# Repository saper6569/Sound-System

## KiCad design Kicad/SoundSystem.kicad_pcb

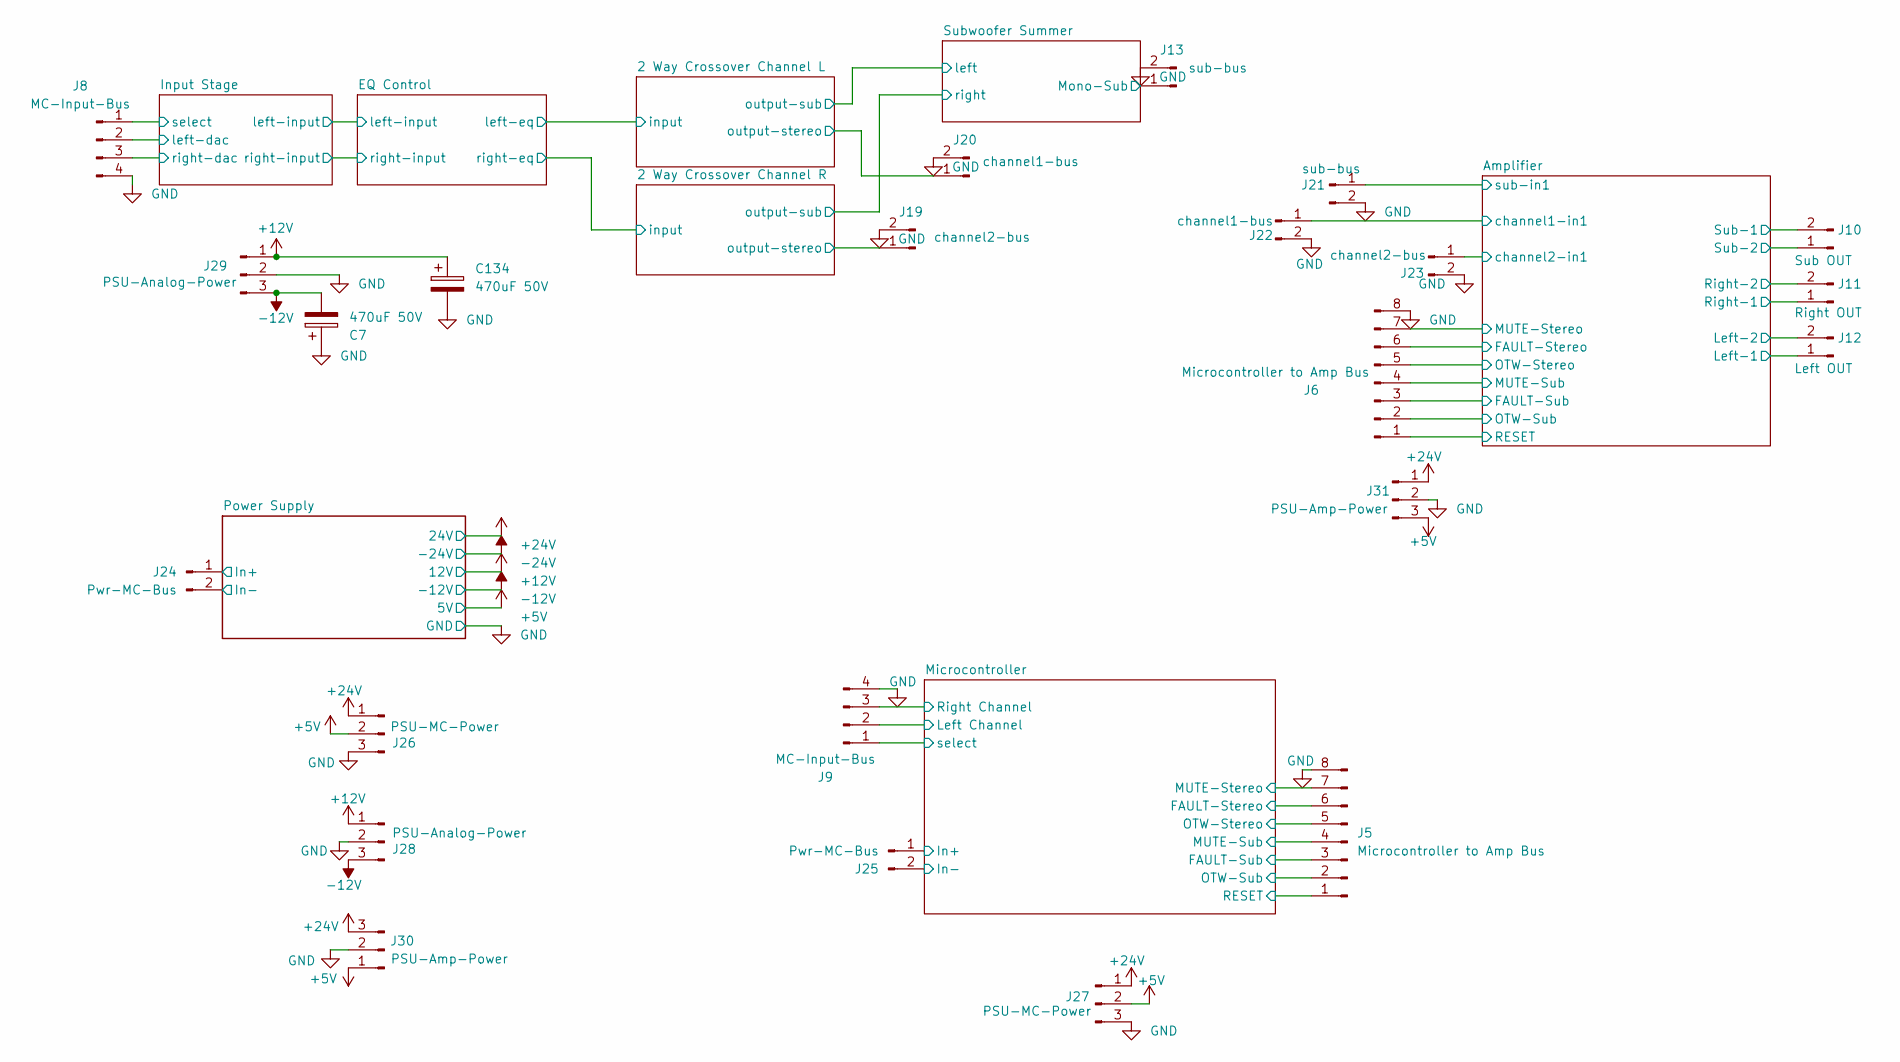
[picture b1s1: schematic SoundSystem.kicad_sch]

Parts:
C7, C134: 470uF 50V; CP_Radial_D12.5mm_P5.00mm; MPN NXH 50V470 12.5*20; LCSC C165672
J5, J6: Microcontroller to Amp Bus; PinHeader_1x08_P2.54mm_Vertical; MPN PZ254V-11-08P; LCSC C492407
J8, J9: MC-Input-Bus; PinHeader_1x04_P2.54mm_Vertical; MPN PZ254V-11-04P; LCSC C492403
J10: Sub OUT; TerminalBlock_Phoenix_MKDS-1,5-2-5.08_1x02_P5.08mm_Horizont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; MPN KF128-5.08-2P-AA; LCSC C474952
J11: Right OUT; TerminalBlock_Phoenix_MKDS-1,5-2-5.08_1x02_P5.08mm_Horizont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; MPN KF128-5.08-2P-AA; LCSC C474952
J12: Left OUT; TerminalBlock_Phoenix_MKDS-1,5-2-5.08_1x02_P5.08mm_Horizont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; MPN KF128-5.08-2P-AA; LCSC C474952
J13, J21: sub-bus; PinHeader_1x02_P2.54mm_Vertical; MPN PZ254V-11-02P; LCSC C492401
J19, J23: channel2-bus; PinHeader_1x02_P2.54mm_Vertical; MPN PZ254V-11-02P; LCSC C492401
J20, J22: channel1-bus; PinHeader_1x02_P2.54mm_Vertical; MPN PZ254V-11-02P; LCSC C492401
J24, J25: Pwr-MC-Bus; PinHeader_1x02_P2.54mm_Vertical; MPN PZ254V-11-02P; LCSC C492401
J26, J27: PSU-MC-Power; PinHeader_1x03_P2.54mm_Vertical; MPN PZ254V-11-03P; LCSC C2937625
J28, J29: PSU-Analog-Power; PinHeader_1x03_P2.54mm_Vertical; MPN PZ254V-11-03P; LCSC C2937625
J30, J31: PSU-Amp-Power; TerminalBlock_Phoenix_MKDS-1,5-3-5.08_1x03_P5.08mm_Horizont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; MPN KF128-5.08-3P-AA; LCSC C474953

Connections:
+12V: C134.1, J28.1, J29.1; also elsewhere on the board
-12V: C7.2, J28.3, J29.3; also elsewhere on the board
/2 Way Crossover Channel L/output-stereo: J20.1; also elsewhere on the board
/2 Way Crossover Channel R/output-stereo: J19.1; also elsewhere on the board
/Amplifier/FAULT-Stereo: J6.6; also elsewhere on the board
/Amplifier/FAULT-Sub: J6.3; also elsewhere on the board
/Amplifier/Left-1: J12.1; also elsewhere on the board
/Amplifier/Left-2: J12.2; also elsewhere on the board
/Amplifier/MUTE-Stereo: J6.7; also elsewhere on the board
/Amplifier/MUTE-Sub: J6.4; also elsewhere on the board
/Amplifier/OTW-Stereo: J6.5; also elsewhere on the board
/Amplifier/OTW-Sub: J6.2; also elsewhere on the board
/Amplifier/Right-1: J11.1; also elsewhere on the board
/Amplifier/Right-2: J11.2; also elsewhere on the board
/Amplifier/Sub-1: J10.2; also elsewhere on the board
/Amplifier/Sub-2: J10.1; also elsewhere on the board
/Amplifier/channel1-in1: J22.1; also elsewhere on the board
/Amplifier/channel2-in1: J23.1; also elsewhere on the board
/Amplifier/sub-in1: J21.1; also elsewhere on the board
/Input Stage/left-dac: J8.2; also elsewhere on the board
/Input Stage/right-dac: J8.3; also elsewhere on the board
/Input Stage/select: J8.1; also elsewhere on the board
/Microcontroller/FAULT-Stereo: J5.5; also elsewhere on the board
/Microcontroller/FAULT-Sub: J5.3; also elsewhere on the board
/Microcontroller/In+: J25.1; also elsewhere on the board
/Microcontroller/In-: J25.2; also elsewhere on the board
/Microcontroller/Left Channel: J9.2; also elsewhere on the board
/Microcontroller/MUTE-Stereo: J5.7; also elsewhere on the board
/Microcontroller/MUTE-Sub: J5.4; also elsewhere on the board
/Microcontroller/OTW-Stereo: J5.6; also elsewhere on the board
/Microcontroller/OTW-Sub: J5.2; also elsewhere on the board
/Microcontroller/RESET: J5.1; also elsewhere on the board
/Microcontroller/Right Channel: J9.3; also elsewhere on the board
/Microcontroller/select: J9.1; also elsewhere on the board
/Power Supply/In+: J24.1; also elsewhere on the board
/Subwoofer Summer/Mono-Sub: J13.1; also elsewhere on the board
GND: C7.1, C134.2, J5.8, J6.8, J8.4, J9.4, J13.2, J19.2, J20.2, J21.2, J22.2, J23.2, J26.3, J27.3, J28.2, J29.2, J30.2, J31.2; also elsewhere on the board
RESET: J6.1; also elsewhere on the board

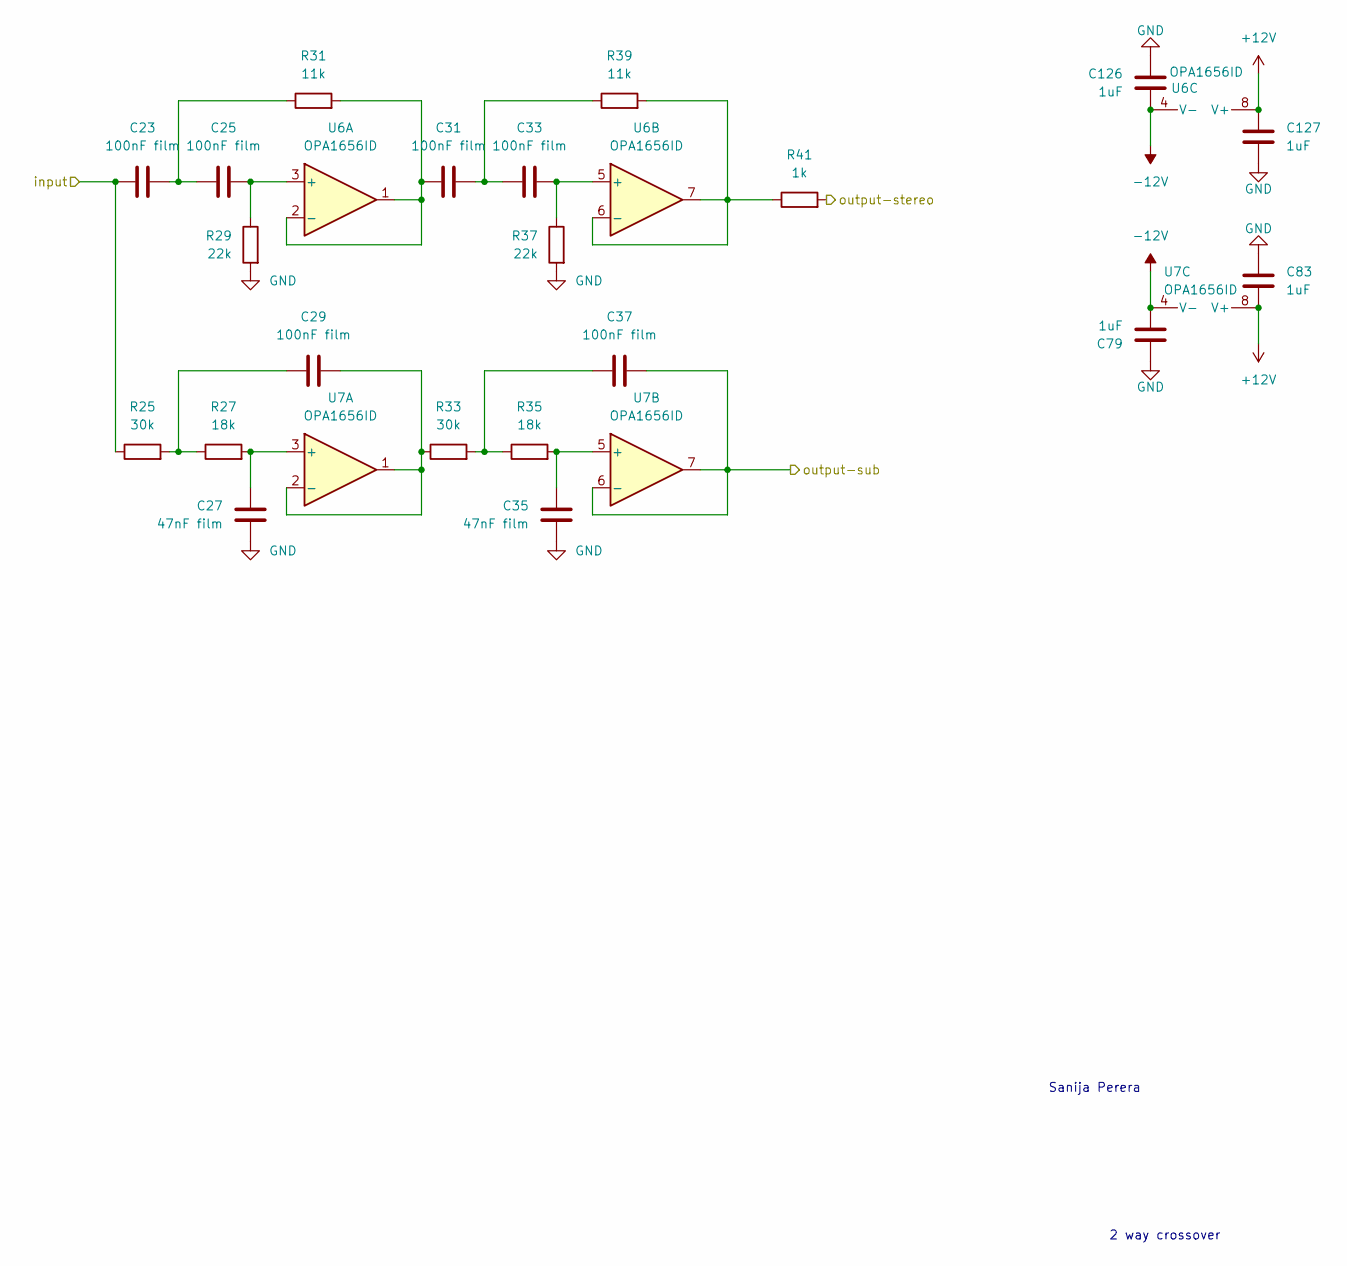
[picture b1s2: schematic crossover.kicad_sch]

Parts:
C23, C25, C29, C31, C33, C37: 100nF film; C_Rect_L7.2mm_W3.5mm_P5.00mm_FKS2_FKP2_MKS2_MKP2; MPN MKS2D031001A00JSSD; LCSC C415551
C27, C35: 47nF film; C_Rect_L7.2mm_W4.5mm_P5.00mm_FKS2_FKP2_MKS2_MKP2; MPN C242A473J20A201; LCSC C328859
C79, C83, C126, C127: 1uF; C_0805_2012Metric_Pad1.18x1.45mm_HandSolder; MPN CC0805KKX7R9BB105; LCSC C91185
R25, R33: 30k; R_0805_2012Metric_Pad1.20x1.40mm_HandSolder; MPN 0805W8F3002T5E; LCSC C17621
R27, R35: 18k; R_0805_2012Metric_Pad1.20x1.40mm_HandSolder; MPN 0805W8F1802T5E; LCSC C17506
R29, R37: 22k; R_0805_2012Metric_Pad1.20x1.40mm_HandSolder; MPN 0805W8F2202T5E; LCSC C17560
R31, R39: 11k; R_0805_2012Metric_Pad1.20x1.40mm_HandSolder; MPN 0805W8F1102T5E; LCSC C17429
R41: 1k; R_0805_2012Metric_Pad1.20x1.40mm_HandSolder; MPN 0805W8F1001T5E; LCSC C17513
U6, U7: OPA1656ID; SOIC-8_3.9x4.9mm_P1.27mm; MPN OPA1656IDR; LCSC C1849431

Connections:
+12V: C83.2, C127.2, U6.8 (V+), U7.8 (V+); also elsewhere on the board
-12V: C79.1, C126.1, U6.4 (V-), U7.4 (V-); also elsewhere on the board
/2 Way Crossover Channel L/input: C23.1, R25.1; also elsewhere on the board
/2 Way Crossover Channel L/output-stereo: R41.2; also elsewhere on the board
/2 Way Crossover Channel L/output-sub: C37.2, U7.6 (-), U7.7; also elsewhere on the board
GND: C27.1, C35.1, C79.2, C83.1, C126.2, C127.1, R29.2, R37.2; also elsewhere on the board
unnamed: C23.2, C25.1, R31.1
unnamed: C29.1, R25.2, R27.1
unnamed: C31.2, C33.1, R39.1
unnamed: C37.1, R33.2, R35.1
unnamed: C25.2, R29.1, U6.3 (+)
unnamed: C31.1, R31.2, U6.1, U6.2 (-)
unnamed: C33.2, R37.1, U6.5 (+)
unnamed: R39.2, R41.1, U6.6 (-), U6.7
unnamed: C27.2, R27.2, U7.3 (+)
unnamed: C29.2, R33.1, U7.1, U7.2 (-)
unnamed: C35.2, R35.2, U7.5 (+)

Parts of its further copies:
C24, C26, C30, C32, C34, C38: 100nF film; C_Rect_L7.2mm_W3.5mm_P5.00mm_FKS2_FKP2_MKS2_MKP2; MPN MKS2D031001A00JSSD; LCSC C415551
C28, C36: 47nF film; C_Rect_L7.2mm_W4.5mm_P5.00mm_FKS2_FKP2_MKS2_MKP2; MPN C242A473J20A201; LCSC C328859
C84, C85, C128, C129: 1uF; C_0805_2012Metric_Pad1.18x1.45mm_HandSolder; MPN CC0805KKX7R9BB105; LCSC C91185
R26, R34: 30k; R_0805_2012Metric_Pad1.20x1.40mm_HandSolder; MPN 0805W8F3002T5E; LCSC C17621
R28, R36: 18k; R_0805_2012Metric_Pad1.20x1.40mm_HandSolder; MPN 0805W8F1802T5E; LCSC C17506
R30, R38: 22k; R_0805_2012Metric_Pad1.20x1.40mm_HandSolder; MPN 0805W8F2202T5E; LCSC C17560
R32, R40: 11k; R_0805_2012Metric_Pad1.20x1.40mm_HandSolder; MPN 0805W8F1102T5E; LCSC C17429
R42: 1k; R_0805_2012Metric_Pad1.20x1.40mm_HandSolder; MPN 0805W8F1001T5E; LCSC C17513
U8, U9: OPA1656ID; SOIC-8_3.9x4.9mm_P1.27mm; MPN OPA1656IDR; LCSC C1849431

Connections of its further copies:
+12V: C85.2, C129.2, U8.8 (V+), U9.8 (V+); also elsewhere on the board
-12V: C84.1, C128.1, U8.4 (V-), U9.4 (V-); also elsewhere on the board
/2 Way Crossover Channel R/input: C24.1, R26.1; also elsewhere on the board
/2 Way Crossover Channel R/output-stereo: R42.2; also elsewhere on the board
/2 Way Crossover Channel R/output-sub: C38.2, U9.6 (-), U9.7; also elsewhere on the board
GND: C28.1, C36.1, C84.2, C85.1, C128.2, C129.1, R30.2, R38.2; also elsewhere on the board
unnamed: C24.2, C26.1, R32.1
unnamed: C30.1, R26.2, R28.1
unnamed: C32.2, C34.1, R40.1
unnamed: C38.1, R34.2, R36.1
unnamed: C26.2, R30.1, U8.3 (+)
unnamed: C32.1, R32.2, U8.1, U8.2 (-)
unnamed: C34.2, R38.1, U8.5 (+)
unnamed: R40.2, R42.1, U8.6 (-), U8.7
unnamed: C28.2, R28.2, U9.3 (+)
unnamed: C30.2, R34.1, U9.1, U9.2 (-)
unnamed: C36.2, R36.2, U9.5 (+)

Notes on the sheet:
2 way crossover
Sanija Perera

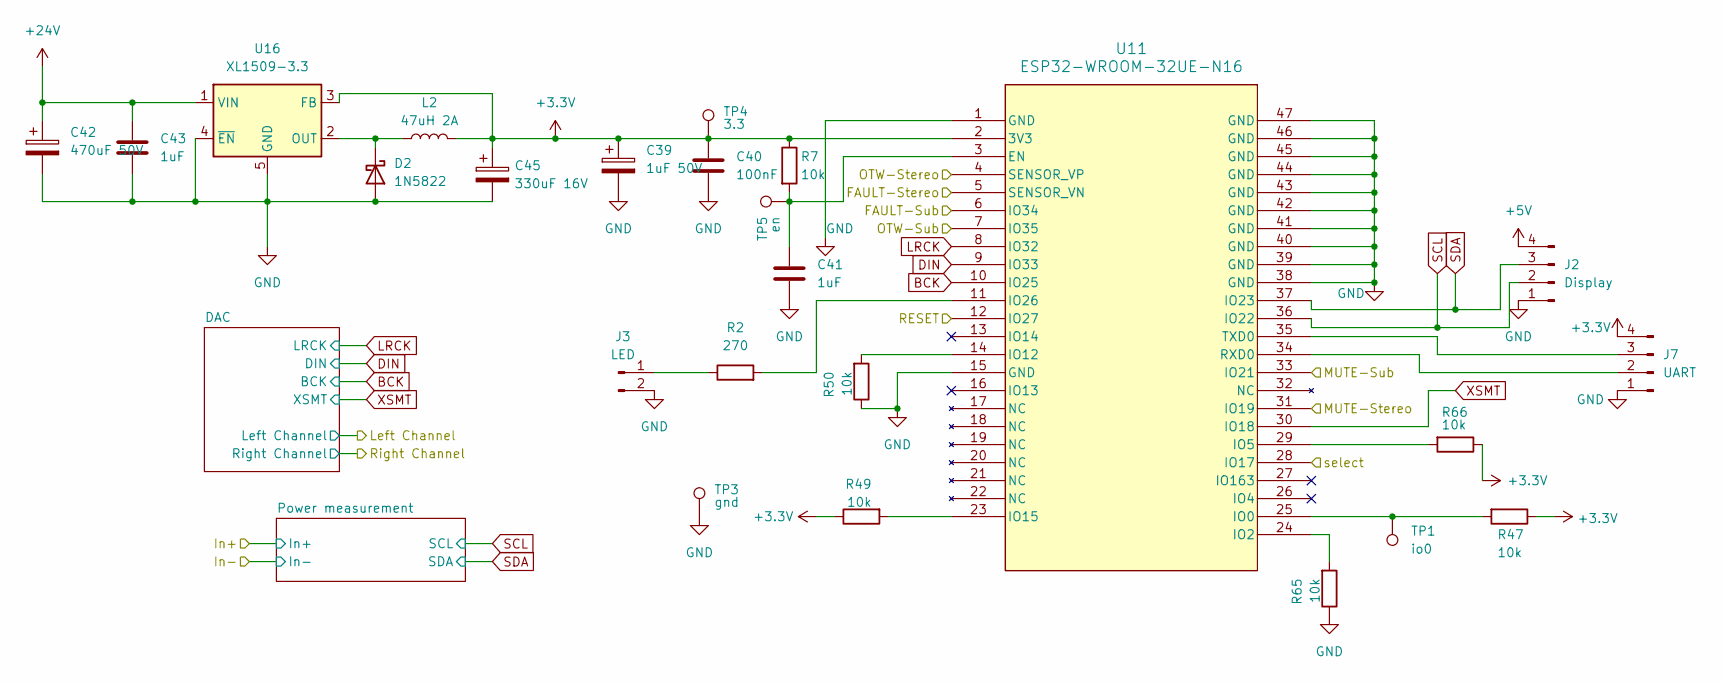
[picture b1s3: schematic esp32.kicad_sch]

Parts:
C39: 1uF 50V; CP_Elec_4x5.4; MPN MVK50V1M4*5 4.0TP; LCSC C346963
C40: 100nF; C_0805_2012Metric_Pad1.18x1.45mm_HandSolder; MPN CC0805KRX7R9BB104; LCSC C49678
C41: 1uF; C_0805_2012Metric_Pad1.18x1.45mm_HandSolder; MPN CC0805KKX7R9BB105; LCSC C91185
C42: 470uF 50V; CP_Radial_D12.5mm_P5.00mm; MPN NXH 50V470 12.5*20; LCSC C165672
C43: 1uF; C_1206_3216Metric_Pad1.33x1.80mm_HandSolder; MPN CC1206KKX7R9BB105; LCSC C107185
C45: 330uF 16V; CP_Elec_8x10; MPN MVK16V330M8*10 8.0TP; LCSC C2835680
D2: 1N5822; D_DO-27_P12.70mm_Horizontal; MPN 1N5822; LCSC C2476
J2: Display; PinHeader_1x04_P2.54mm_Vertical; MPN PZ254V-11-04P; LCSC C492403
J3: LED; PinHeader_1x02_P2.54mm_Vertical; MPN PZ254V-11-02P; LCSC C492401
J7: UART; PinHeader_1x04_P2.54mm_Vertical; MPN PZ254V-11-04P; LCSC C492403
L2: 47uH 2A; L_Bourns_SRR1260; MPN SRR1260-470M; LCSC C1329363
R2: 270; R_0805_2012Metric_Pad1.20x1.40mm_HandSolder; MPN 0805W8F2700T5E; LCSC C17590
R7, R47, R49, R50, R65, R66: 10k; R_0805_2012Metric_Pad1.20x1.40mm_HandSolder; MPN 0805W8F1002T5E; LCSC C17414
TP1: io0; TestPoint_Pad_1.0x1.0mm; MPN (PCB pad)
TP3: gnd; TestPoint_Pad_1.0x1.0mm; MPN (PCB pad)
TP4: 3.3; TestPoint_Pad_1.0x1.0mm; MPN (PCB pad)
TP5: en; TestPoint_Pad_1.0x1.0mm; MPN (PCB pad)
U11: ESP32-WROOM-32UE-N16; ESP32-32UE_EXP; MPN ESP32-WROOM-32UE-N16; LCSC C701346
U16: XL1509-3.3; SOIC-8_3.9x4.9mm_P1.27mm; MPN XL1509-3.3E1; LCSC C74193

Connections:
+3.3V: C39.1, C40.1, C45.1, J7.4, L2.2, R7.1, R47.1, R49.1, R66.1, TP4.1 (1_1), U11.2 (3V3), U16.3 (FB); also elsewhere on the board
/Microcontroller/FAULT-Stereo: U11.5 (SENSOR_VN); also elsewhere on the board
/Microcontroller/FAULT-Sub: U11.6 (IO34); also elsewhere on the board
/Microcontroller/MUTE-Stereo: U11.31 (IO19); also elsewhere on the board
/Microcontroller/MUTE-Sub: U11.33 (IO21); also elsewhere on the board
/Microcontroller/OTW-Stereo: U11.4 (SENSOR_VP); also elsewhere on the board
/Microcontroller/OTW-Sub: U11.7 (IO35); also elsewhere on the board
/Microcontroller/RESET: U11.12 (IO27); also elsewhere on the board
/Microcontroller/select: U11.28 (IO17); also elsewhere on the board
BCK: U11.10 (IO25); also elsewhere on the board
DIN: U11.9 (IO33); also elsewhere on the board
GND: C39.2, C40.2, C41.2, C42.2, C43.2, C45.2, D2.2 (A), J2.1, J3.2, J7.1, R50.1, R65.1, TP3.1 (1_1), U11.1 (GND), U11.15 (GND), U11.38 (GND), U11.39 (GND), U11.40 (GND), U11.41 (GND), U11.42 (GND), U11.43 (GND), U11.44 (GND), U11.45 (GND), U11.46 (GND), U11.47 (GND), U16.4 (~EN), U16.5 (GND), U16.6 (GND), U16.7 (GND), U16.8 (GND); also elsewhere on the board
LRCK: U11.8 (IO32); also elsewhere on the board
unnamed: D2.1 (K), L2.1, U16.2 (OUT)
unnamed: J3.1, R2.1
unnamed: J7.2, U11.34 (RXD0)
unnamed: J7.3, U11.35 (TXD0)
unnamed: C41.1, R7.2, TP5.1 (1_1), U11.3 (EN)
unnamed: R47.2, TP1.1 (1_1), U11.25 (IO0)
unnamed: R65.2, U11.24 (IO2)
unnamed: R66.2, U11.29 (IO5)
unnamed: R50.2, U11.14 (IO12)
unnamed: R49.2, U11.23 (IO15)
unnamed: R2.2, U11.11 (IO26)
SCL: J2.2, U11.36 (IO22); also elsewhere on the board
SDA: J2.3, U11.37 (IO23); also elsewhere on the board
XSMT: U11.30 (IO18); also elsewhere on the board

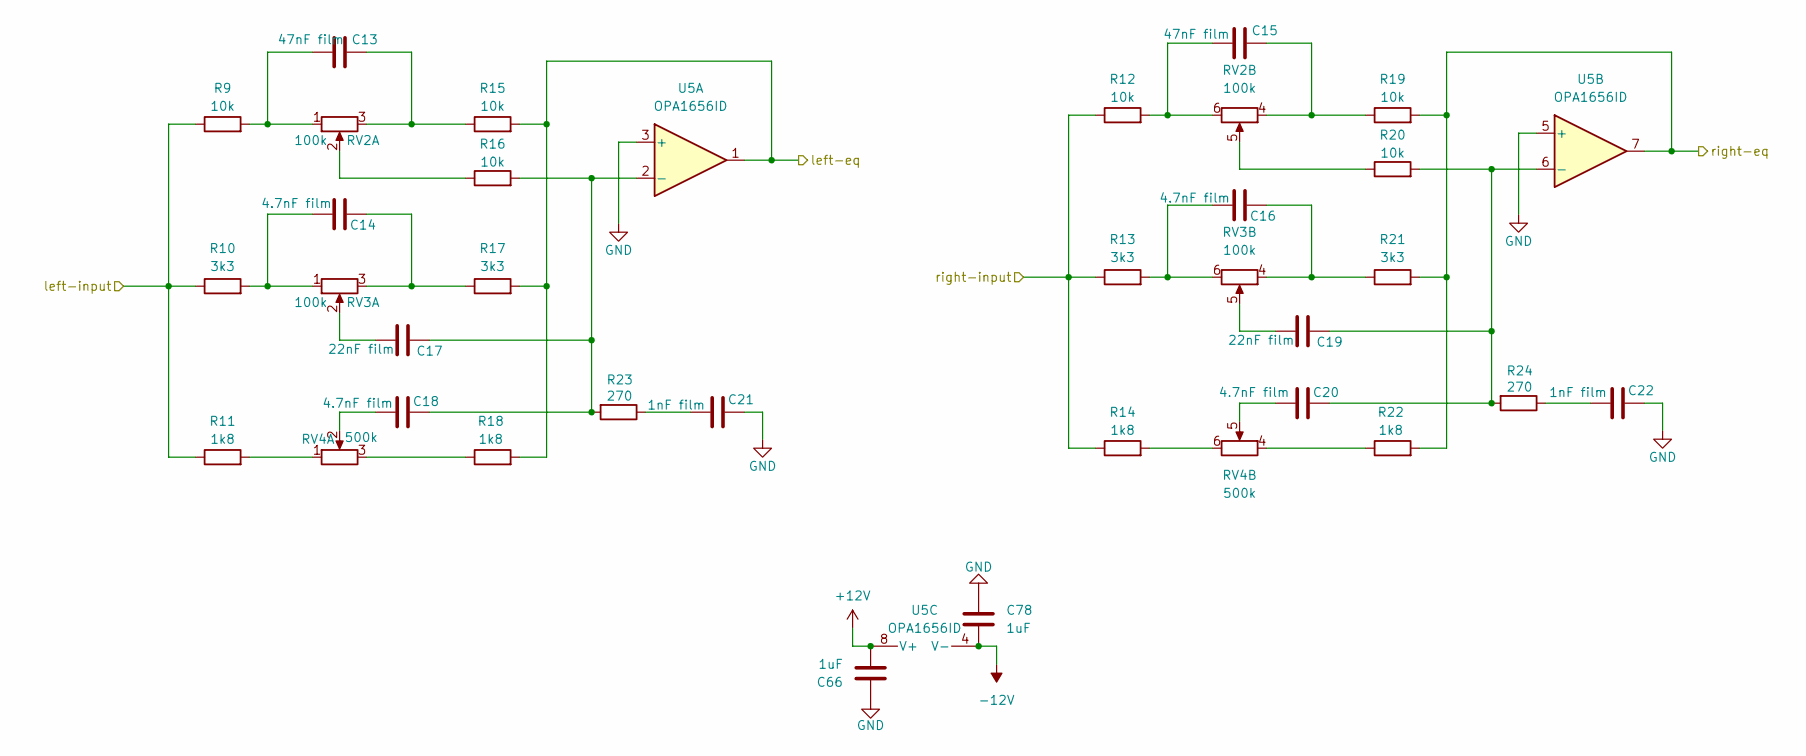
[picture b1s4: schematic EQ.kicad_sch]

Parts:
C13, C15: 47nF film; C_Rect_L7.2mm_W4.5mm_P5.00mm_FKS2_FKP2_MKS2_MKP2; MPN C242A473J20A201; LCSC C328859
C14, C16, C18, C20: 4.7nF film; C_Rect_L7.2mm_W3.5mm_P5.00mm_FKS2_FKP2_MKS2_MKP2; MPN C242A472J20A201; LCSC C401257
C17, C19: 22nF film; C_Rect_L7.2mm_W3.5mm_P5.00mm_FKS2_FKP2_MKS2_MKP2; MPN C242A223J20A201; LCSC C328834
C21, C22: 1nF film; C_Rect_L7.2mm_W3.5mm_P5.00mm_FKS2_FKP2_MKS2_MKP2; MPN C242A102J20C000; LCSC C280714
C66, C78: 1uF; C_0805_2012Metric_Pad1.18x1.45mm_HandSolder; MPN CC0805KKX7R9BB105; LCSC C91185
R9, R12, R15, R16, R19, R20: 10k; R_0805_2012Metric_Pad1.20x1.40mm_HandSolder; MPN 0805W8F1002T5E; LCSC C17414
R10, R13, R17, R21: 3k3; R_0805_2012Metric_Pad1.20x1.40mm_HandSolder; MPN 0805W8F3301T5E; LCSC C26010
R11, R14, R18, R22: 1k8; R_1206_3216Metric_Pad1.30x1.75mm_HandSolder; MPN 1206W4F1801T5E; LCSC C22108
R23, R24: 270; R_0805_2012Metric_Pad1.20x1.40mm_HandSolder; MPN 0805W8F2700T5E; LCSC C17590
RV2, RV3: 100k; 10k pot; MPN 16mm dual-gang pot (A10K / B100K / B100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
RV4: 500k; 10k pot; MPN 16mm dual-gang pot (A10K / B100K / B100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
U5: OPA1656ID; SOIC-8_3.9x4.9mm_P1.27mm; MPN OPA1656IDR; LCSC C1849431

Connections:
+12V: C66.1, U5.8 (V+); also elsewhere on the board
-12V: C78.2, U5.4 (V-); also elsewhere on the board
/2 Way Crossover Channel L/input: R15.2, R17.2, R18.2, U5.1; also elsewhere on the board
/2 Way Crossover Channel R/input: R19.2, R21.2, R22.2, U5.7; also elsewhere on the board
/EQ Control/left-input: R9.1, R10.1, R11.1; also elsewhere on the board
/EQ Control/right-input: R12.1, R13.1, R14.1; also elsewhere on the board
GND: C21.1, C22.1, C66.2, C78.1, U5.3 (+), U5.5 (+); also elsewhere on the board
unnamed: C13.1, R9.2, RV2.1
unnamed: C13.2, R15.1, RV2.3
unnamed: C14.1, R10.2, RV3.1
unnamed: C14.2, R17.1, RV3.3
unnamed: C15.1, R12.2, RV2.6
unnamed: C15.2, R19.1, RV2.4
unnamed: C16.1, R13.2, RV3.6
unnamed: C16.2, R21.1, RV3.4
unnamed: C17.1, RV3.2
unnamed: C18.1, RV4.2
unnamed: C19.1, RV3.5
unnamed: C20.1, RV4.5
unnamed: C21.2, R23.1
unnamed: C22.2, R24.1
unnamed: R11.2, RV4.1
unnamed: R14.2, RV4.6
unnamed: R16.1, RV2.2
unnamed: R18.1, RV4.3
unnamed: R20.1, RV2.5
unnamed: R22.1, RV4.4
unnamed: C17.2, C18.2, R16.2, R23.2, U5.2 (-)
unnamed: C19.2, C20.2, R20.2, R24.2, U5.6 (-)

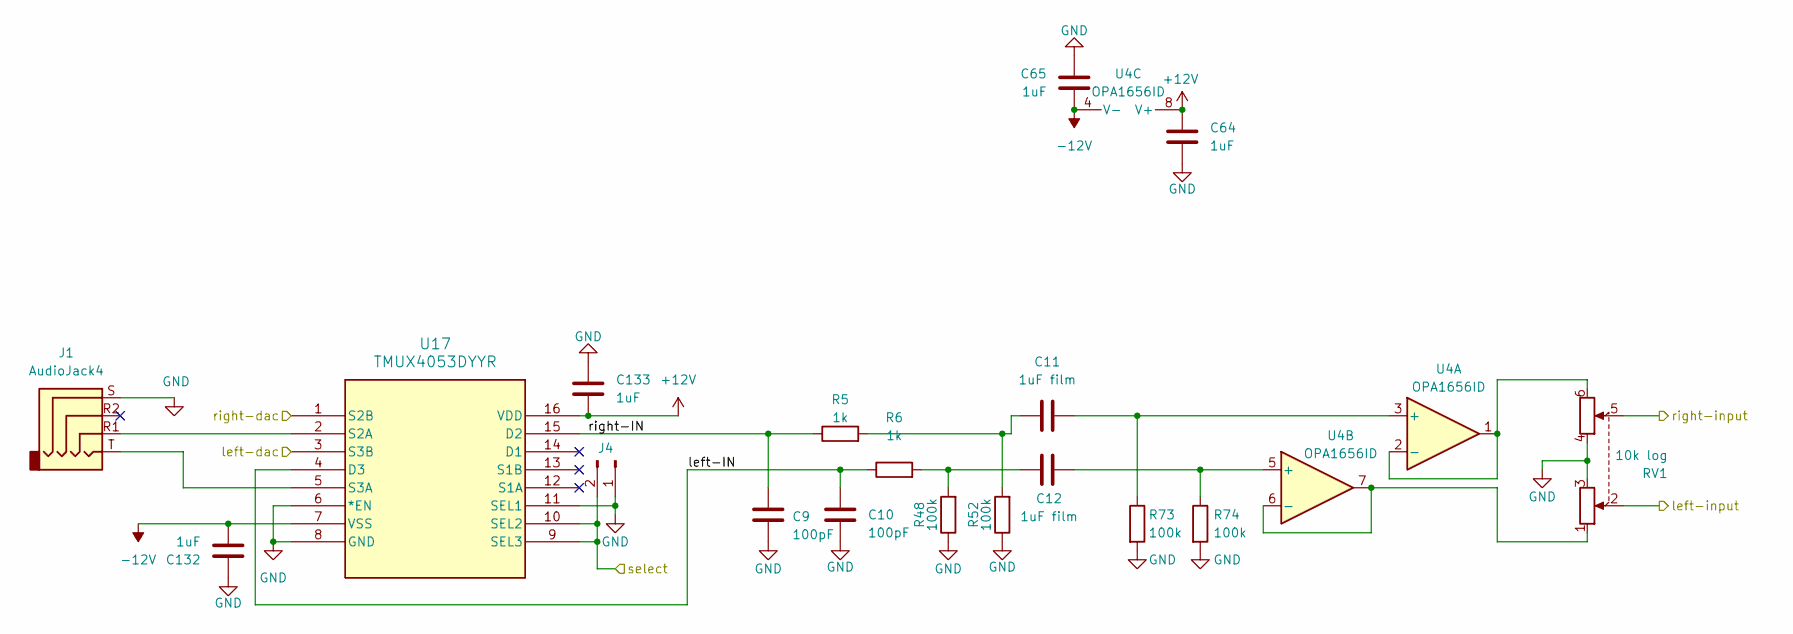
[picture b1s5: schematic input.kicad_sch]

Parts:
C9, C10: 100pF; C_0805_2012Metric_Pad1.18x1.45mm_HandSolder; MPN CC0805JRNPO9BN101; LCSC C62768
C11, C12: 1uF film; C_Rect_L7.2mm_W5.5mm_P5.00mm_FKS2_FKP2_MKS2_MKP2; MPN B32529C0105J289; LCSC C125386
C64, C65, C132, C133: 1uF; C_0805_2012Metric_Pad1.18x1.45mm_HandSolder; MPN CC0805KKX7R9BB105; LCSC C91185
J1: AudioJack4; Jack_3.5mm_KoreanHropartsElec_PJ-320D-4A_Horizontal; MPN PJ-320D-4A; LCSC C95562
J4: Conn_01x02_Pin; PinHeader_1x02_P2.54mm_Vertical; MPN PZ254V-11-02P; LCSC C492401
R5, R6: 1k; R_0805_2012Metric_Pad1.20x1.40mm_HandSolder; MPN 0805W8F1001T5E; LCSC C17513
R48, R52, R73, R74: 100k; R_0805_2012Metric_Pad1.20x1.40mm_HandSolder; MPN 0805W8F1003T5E; LCSC C17407
RV1: 10k log; 10k pot; MPN 16mm dual-gang pot (A10K / B100K / B100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
U4: OPA1656ID; SOIC-8_3.9x4.9mm_P1.27mm; MPN OPA1656IDR; LCSC C1849431
U17: TMUX4053DYYR; C22388988_SOT-23-THIN-16_L4_2-W2_0-P0_50-LS3_2-BR; MPN TMUX4053DYYR; LCSC C22388988

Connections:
+12V: C64.2, C133.2, U4.8 (V+), U17.16 (VDD); also elsewhere on the board
-12V: C65.1, C132.1, U4.4 (V-), U17.7 (VSS); also elsewhere on the board
/EQ Control/left-input: RV1.2; also elsewhere on the board
/EQ Control/right-input: RV1.5; also elsewhere on the board
/Input Stage/left-IN: C10.1, R6.1, U17.4 (D3)
/Input Stage/left-dac: U17.3 (S3B); also elsewhere on the board
/Input Stage/right-IN: C9.1, R5.1, U17.15 (D2)
/Input Stage/right-dac: U17.1 (S2B); also elsewhere on the board
/Input Stage/select: J4.2, U17.9 (SEL3), U17.10 (SEL2); also elsewhere on the board
GND: C9.2, C10.2, C64.1, C65.2, C132.2, C133.1, J1.S, J4.1, R48.1, R52.1, R73.2, R74.2, RV1.3, RV1.4, U17.6 (*EN), U17.8 (GND), U17.11 (SEL1); also elsewhere on the board
unnamed: C11.1, R5.2, R52.2
unnamed: C12.1, R6.2, R48.2
unnamed: C11.2, R73.1, U4.3 (+)
unnamed: RV1.6, U4.1, U4.2 (-)
unnamed: C12.2, R74.1, U4.5 (+)
unnamed: RV1.1, U4.6 (-), U4.7
unnamed: J1.R1, U17.2 (S2A)
unnamed: J1.T, U17.5 (S3A)

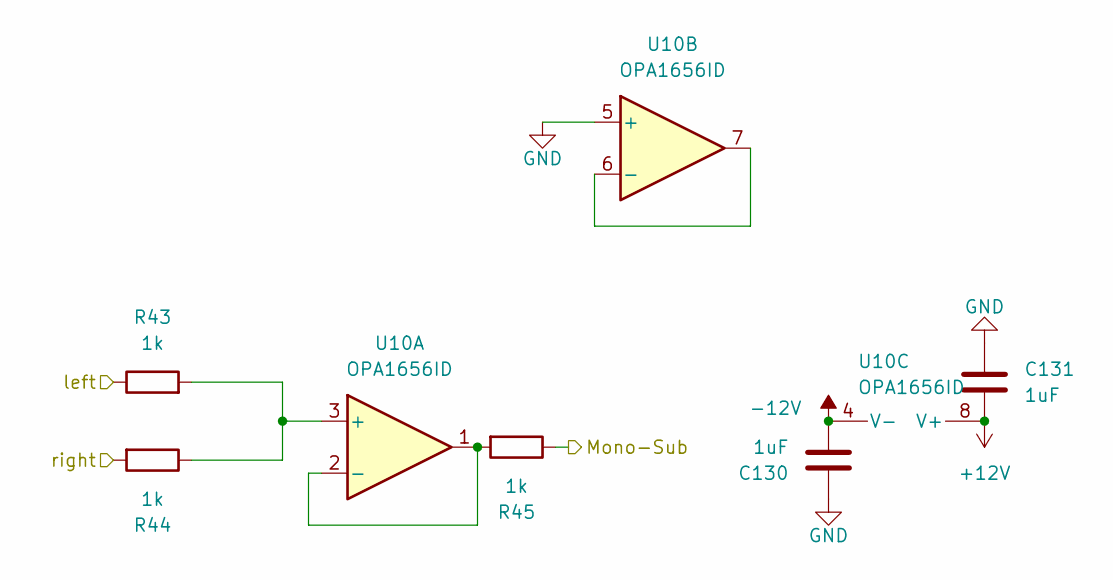
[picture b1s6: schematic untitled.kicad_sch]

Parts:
C130, C131: 1uF; C_0805_2012Metric_Pad1.18x1.45mm_HandSolder; MPN CC0805KKX7R9BB105; LCSC C91185
R43, R44, R45: 1k; R_0805_2012Metric_Pad1.20x1.40mm_HandSolder; MPN 0805W8F1001T5E; LCSC C17513
U10: OPA1656ID; SOIC-8_3.9x4.9mm_P1.27mm; MPN OPA1656IDR; LCSC C1849431

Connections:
+12V: C131.2, U10.8 (V+); also elsewhere on the board
-12V: C130.1, U10.4 (V-); also elsewhere on the board
/2 Way Crossover Channel L/output-sub: R43.1; also elsewhere on the board
/2 Way Crossover Channel R/output-sub: R44.2; also elsewhere on the board
/Subwoofer Summer/Mono-Sub: R45.1; also elsewhere on the board
GND: C130.2, C131.1, U10.5 (+); also elsewhere on the board
unnamed: R43.2, R44.1, U10.3 (+)
unnamed: R45.2, U10.1, U10.2 (-)
unnamed: U10.6 (-), U10.7

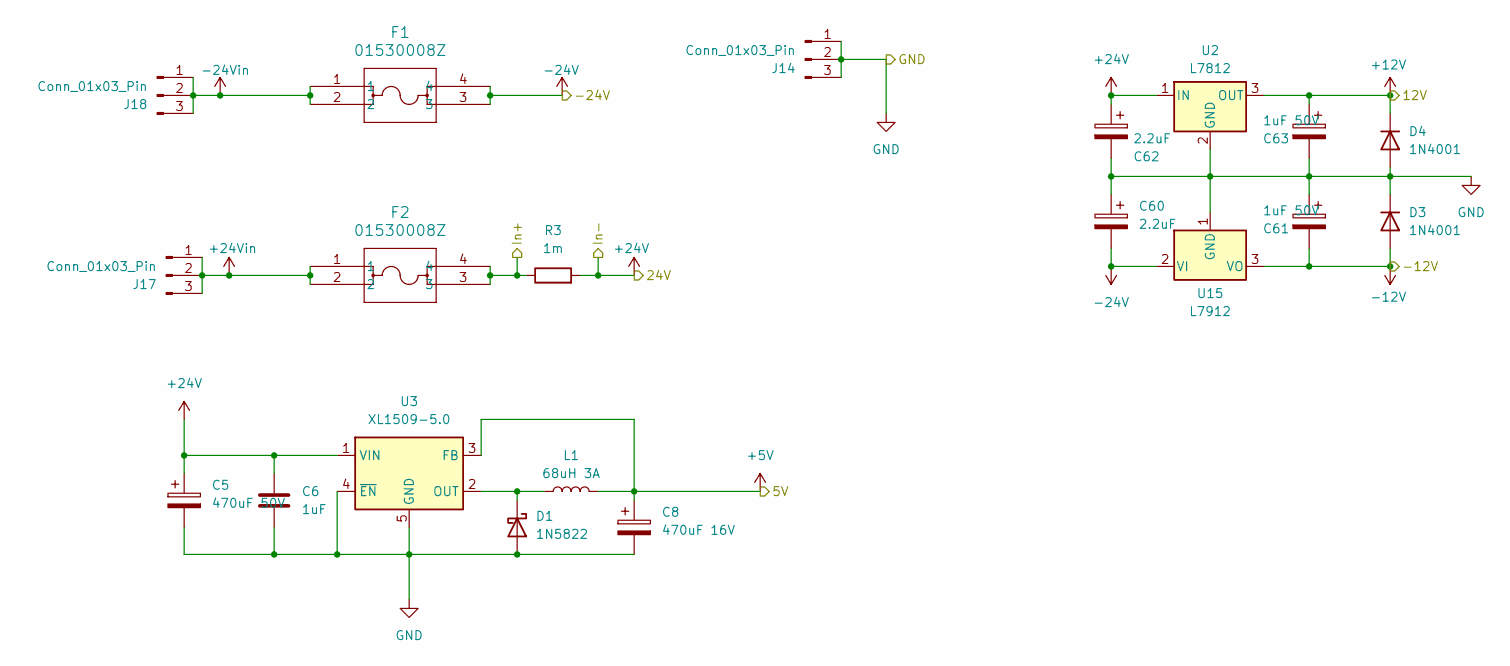
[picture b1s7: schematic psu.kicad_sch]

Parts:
C5: 470uF 50V; CP_Radial_D12.5mm_P5.00mm; MPN NXH 50V470 12.5*20; LCSC C165672
C6: 1uF; C_1206_3216Metric_Pad1.33x1.80mm_HandSolder; MPN CC1206KKX7R9BB105; LCSC C107185
C8: 470uF 16V; CP_Elec_10x10; MPN RYRVT16V470UF10*10; LCSC C48970774
C60, C62: 2.2uF; C_1206_3216Metric_Pad1.33x1.80mm_HandSolder; MPN CC1206KKX7R9BB225; LCSC C133050
C61, C63: 1uF 50V; CP_Elec_4x5.4; MPN MVK50V1M4*5 4.0TP; LCSC C346963
D1: 1N5822; D_DO-27_P12.70mm_Horizontal; MPN 1N5822; LCSC C2476
D3, D4: 1N4001; D_SMA_Handsoldering; MPN 1N4001; LCSC C727079
F1, F2: 01530008Z; Fuseholder_Blade_Mini_Littelfuse_01530008; MPN 01530008Z; LCSC C206907
J14, J17, J18: Conn_01x03_Pin; TerminalBlock_Phoenix_MKDS-1,5-3-5.08_1x03_P5.08mm_Horizont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; MPN KF128-5.08-3P-AA; LCSC C474953
L1: 68uH 3A; L_Bourns_SRR1210A; MPN SRR1210-680M; LCSC C2041823
R3: 1m; R_2512_6332Metric_Pad1.40x3.35mm_HandSolder; MPN LR2512D-3W-1mR-1%; LCSC C500734
U2: L7812; TO-220-3_Vertical; MPN L7812CV-DG; LCSC C2914
U3: XL1509-5.0; SOIC-8_3.9x4.9mm_P1.27mm; MPN XL1509-5.0E1; LCSC C61063
U15: L7912; TO-220-3_Vertical; MPN L7912CV-DG; LCSC C3797

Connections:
+12V: C63.1, D4.1 (K), U2.3 (OUT); also elsewhere on the board
+24Vin: F2.1, F2.2, J17.1, J17.2, J17.3
-12V: C61.2, D3.2 (A), U15.3 (VO); also elsewhere on the board
-24V: C60.2, F1.3, F1.4, U15.2 (VI)
-24Vin: F1.1, F1.2, J18.1, J18.2, J18.3
/Power Supply/In+: F2.3, F2.4, R3.1; also elsewhere on the board
GND: C5.2, C6.2, C8.2, C60.1, C61.1, C62.2, C63.2, D1.2 (A), D3.1 (K), D4.2 (A), J14.1, J14.2, J14.3, U2.2 (GND), U3.4 (~EN), U3.5 (GND), U3.6 (GND), U3.7 (GND), U3.8 (GND), U15.1 (GND); also elsewhere on the board
unnamed: D1.1 (K), L1.1, U3.2 (OUT)
